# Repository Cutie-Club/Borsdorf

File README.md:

# Borsdorf
KiCad project files for the Borsdorf keyboard.

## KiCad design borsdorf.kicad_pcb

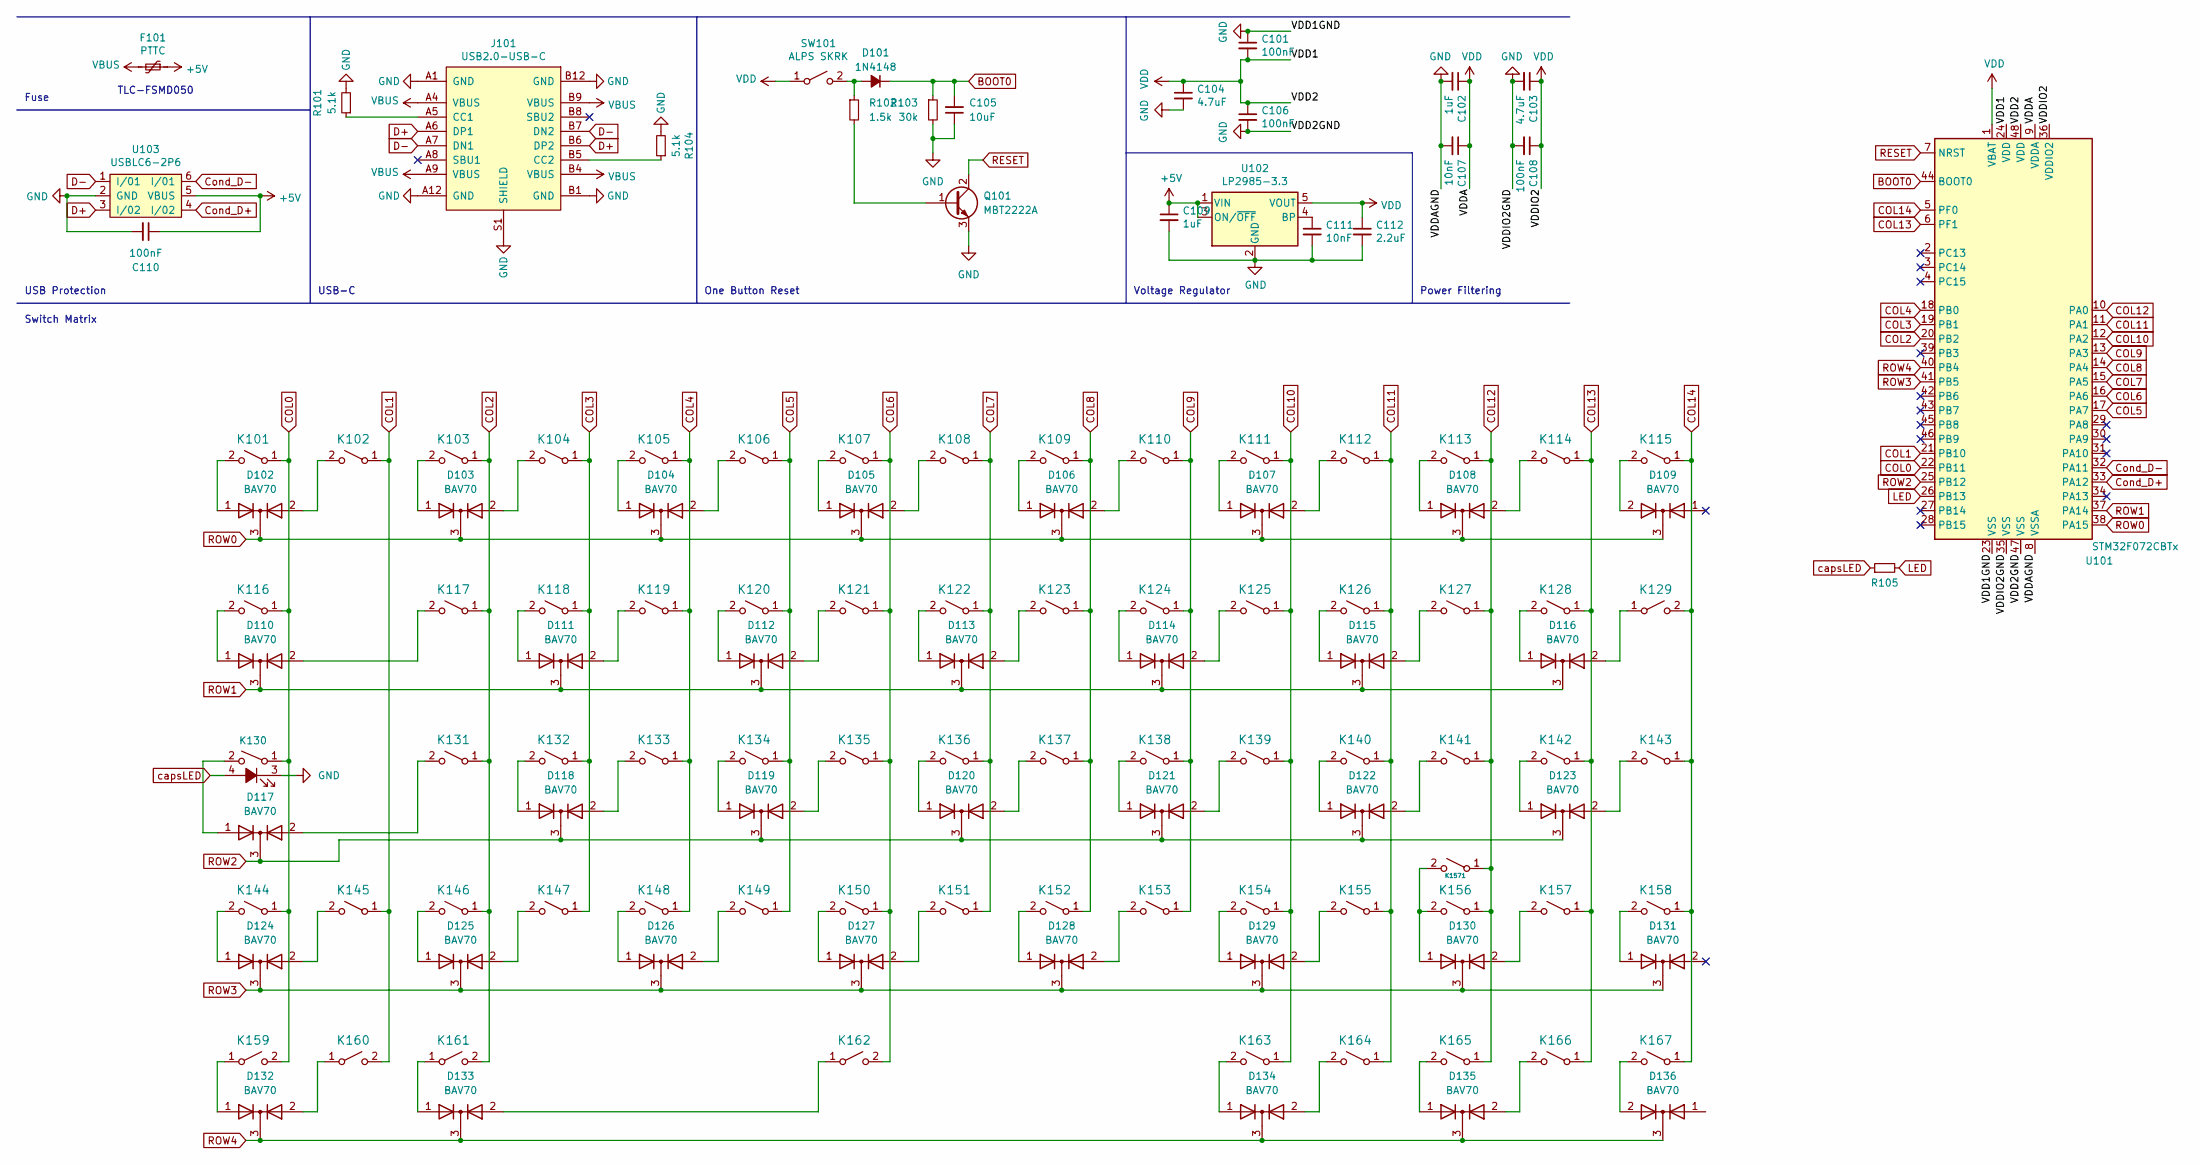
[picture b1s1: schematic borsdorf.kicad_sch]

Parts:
C101, C106, C108, C110: 100nF; C_0805_2012Metric
C102, C109: 1uF; C_0805_2012Metric
C103, C104: 4.7uF; C_0805_2012Metric
C105: 10uF; C_0805_2012Metric
C107, C111: 10nF; C_0805_2012Metric
C112: 2.2uF; C_0805_2012Metric
D101: 1N4148; D_SOD-323
D102, D103, D104, D105, D106, D107, D108, D109, D110, D111, D112, D113, D114, D115, D116, D117, D118, D119, D120, D121, D122, D123, D124, D125, D126, D127, D128, D129, D130, D131, D132, D133, D134, D135, D136: BAV70; SOT-23
F101: PTTC; Fuse_0805_2012Metric
J101: USB2.0-USB-C; USB_C_Receptacle_HRO_TYPE-C-31-M-12
K101, K102, K103, K104, K105, K106, K107, K108, K109, K110, K111, K112, K113, K114, K115, K116, K117, K118, K119, K120, K121, K122, K123, K124, K125, K126, K127, K128, K129, K131, K132, K133, K134, K135, K136, K137, K138, K139, K140, K141, K142, K143, K144, K145, K146, K147, K148, K149, K150, K151, K152, K153, K154, K155, K156, K157, K158, K159, K160, K161, K162, K163, K164, K165, K166, K167, K1571: KEYSW; Alps_SKxx_19.05mm_1.0u
K130: KEYSW; Alps_SKxx_LED_19.05mm_1.0u
Q101: MBT2222A; SOT-23-3
R101, R104: 5.1k; R_0805_2012Metric
R102: 1.5k; R_0805_2012Metric
R103: 30k; R_0805_2012Metric
R105: R_Small; R_0805_2012Metric
SW101: ALPS SKRK; ALPS_SKRK
U101: STM32F072CBTx; LQFP-48_7x7mm_P0.5mm
U102: LP2985-3.3; SOT-23-5
U103: USBLC6-2P6; SOT-23-6

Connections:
+5V: C109.1, C110.1, F101.1, U102.1 (VIN), U102.3 (ON/~OFF), U103.5 (VBUS)
BOOT0: C105.2, D101.1 (K), R103.1, U101.44 (BOOT0)
COL0: K101.1 (A), K116.1 (A), K130.1, K144.1 (A), K159.2 (B), U101.22 (PB11)
COL1: K102.1 (A), K145.1 (A), K160.2 (B), U101.21 (PB10)
COL2: K103.1 (A), K117.1 (A), K131.1 (A), K146.1 (A), K161.2 (B), U101.20 (PB2)
COL3: K104.1 (A), K118.1 (A), K132.1 (A), K147.1 (A), U101.19 (PB1)
COL4: K105.1 (A), K119.1 (A), K133.1 (A), K148.1 (A), U101.18 (PB0)
COL5: K106.1 (A), K120.1 (A), K134.1 (A), K149.1 (A), U101.17 (PA7)
COL6: K107.1 (A), K121.1 (A), K135.1 (A), K150.1 (A), K162.2 (B), U101.16 (PA6)
COL7: K108.1 (A), K122.1 (A), K136.1 (A), K151.1 (A), U101.15 (PA5)
COL8: K109.1 (A), K123.1 (A), K137.1 (A), K152.1 (A), U101.14 (PA4)
COL9: K110.1 (A), K124.1 (A), K138.1 (A), K153.1 (A), U101.13 (PA3)
COL10: K111.1 (A), K125.1 (A), K139.1 (A), K154.1 (A), K163.1 (A), U101.12 (PA2)
COL11: K112.1 (A), K126.1 (A), K140.1 (A), K155.1 (A), K164.1 (A), U101.11 (PA1)
COL12: K113.1 (A), K127.1 (A), K141.1 (A), K156.1 (A), K165.1 (A), K1571.1 (A), U101.10 (PA0)
COL13: K114.1 (A), K128.1 (A), K142.1 (A), K157.1 (A), K166.1 (A), U101.6 (PF1)
COL14: K115.1 (A), K129.2 (B), K143.1 (A), K158.1 (A), K167.1 (A), U101.5 (PF0)
Cond_D+: U101.33 (PA12), U103.4 (I/02)
Cond_D-: U101.32 (PA11), U103.6 (I/01)
D+: J101.A6 (DP1), J101.B6 (DP2), U103.3 (I/02)
D-: J101.A7 (DN1), J101.B7 (DN2), U103.1 (I/01)
GND: C101.1, C102.2, C103.2, C104.2, C105.1, C106.2, C107.2, C108.2, C109.2, C110.2, C111.2, C112.2, J101.A1 (GND), J101.A12 (GND), J101.B1 (GND), J101.B12 (GND), J101.S1 (SHIELD), K130.3 (K), Q101.3 (E), R101.2, R103.2, R104.2, U101.8 (VSSA), U101.23 (VSS), U101.35 (VSS), U101.47 (VSS), U102.2 (GND), U103.2 (GND)
LED: R105.2, U101.26 (PB13)
unnamed: C111.1, U102.4 (BP)
unnamed: D101.2 (A), R102.1, SW101.2 (B)
unnamed: D102.1 (A), K101.2 (B)
unnamed: D102.2 (A), K102.2 (B)
unnamed: D103.1 (A), K103.2 (B)
unnamed: D103.2 (A), K104.2 (B)
unnamed: D104.1 (A), K105.2 (B)
unnamed: D104.2 (A), K106.2 (B)
unnamed: D105.1 (A), K107.2 (B)
unnamed: D105.2 (A), K108.2 (B)
unnamed: D106.1 (A), K109.2 (B)
unnamed: D106.2 (A), K110.2 (B)
unnamed: D107.1 (A), K111.2 (B)
unnamed: D107.2 (A), K112.2 (B)
unnamed: D108.1 (A), K113.2 (B)
unnamed: D108.2 (A), K114.2 (B)
unnamed: D109.2 (A), K115.2 (B)
unnamed: D110.1 (A), K116.2 (B)
unnamed: D110.2 (A), K117.2 (B)
unnamed: D111.1 (A), K118.2 (B)
unnamed: D111.2 (A), K119.2 (B)
unnamed: D112.1 (A), K120.2 (B)
unnamed: D112.2 (A), K121.2 (B)
unnamed: D113.1 (A), K122.2 (B)
unnamed: D113.2 (A), K123.2 (B)
unnamed: D114.1 (A), K124.2 (B)
unnamed: D114.2 (A), K125.2 (B)
unnamed: D115.1 (A), K126.2 (B)
unnamed: D115.2 (A), K127.2 (B)
unnamed: D116.1 (A), K128.2 (B)
unnamed: D116.2 (A), K129.1 (A)
unnamed: D117.1 (A), K130.2
unnamed: D117.2 (A), K131.2 (B)
unnamed: D119.1 (A), K134.2 (B)
unnamed: D119.2 (A), K135.2 (B)
unnamed: D120.1 (A), K136.2 (B)
unnamed: D120.2 (A), K137.2 (B)
unnamed: D121.1 (A), K138.2 (B)
unnamed: D121.2 (A), K139.2 (B)
unnamed: D122.1 (A), K140.2 (B)
unnamed: D122.2 (A), K141.2 (B)
unnamed: D124.1 (A), K144.2 (B)
unnamed: D124.2 (A), K145.2 (B)
unnamed: D125.1 (A), K146.2 (B)
unnamed: D125.2 (A), K147.2 (B)
unnamed: D126.1 (A), K148.2 (B)
unnamed: D126.2 (A), K149.2 (B)
unnamed: D127.1 (A), K150.2 (B)
unnamed: D127.2 (A), K151.2 (B)
unnamed: D128.1 (A), K152.2 (B)
unnamed: D128.2 (A), K153.2 (B)
unnamed: D129.1 (A), K154.2 (B)
unnamed: D129.2 (A), K155.2 (B)
unnamed: D130.1 (A), K156.2 (B), K1571.2 (B)
unnamed: D130.2 (A), K157.2 (B)
unnamed: D131.1 (A), K158.2 (B)
unnamed: D132.1 (A), K159.1 (A)
unnamed: D132.2 (A), K160.1 (A)
unnamed: D133.1 (A), K161.1 (A)
unnamed: D133.2 (A), K162.1 (A)
unnamed: D134.1 (A), K163.2 (B)
unnamed: D134.2 (A), K164.2 (B)
unnamed: D135.1 (A), K165.2 (B)
unnamed: D135.2 (A), K166.2 (B)
unnamed: D136.2 (A), K167.2 (B)
unnamed: J101.A5 (CC1), R101.1
unnamed: J101.B5 (CC2), R104.1
unnamed: D118.1 (A), K132.2 (B)
unnamed: D118.2 (A), K133.2 (B)
unnamed: D123.1 (A), K142.2 (B)
unnamed: D123.2 (A), K143.2 (B)
unnamed: Q101.1 (B), R102.2
RESET: Q101.2 (C), U101.7 (NRST)
ROW0: D102.3 (K), D103.3 (K), D104.3 (K), D105.3 (K), D106.3 (K), D107.3 (K), D108.3 (K), D109.3 (K), U101.38 (PA15)
ROW1: D110.3 (K), D111.3 (K), D112.3 (K), D113.3 (K), D114.3 (K), D115.3 (K), D116.3 (K), U101.37 (PA14)
ROW2: D117.3 (K), D118.3 (K), D119.3 (K), D120.3 (K), D121.3 (K), D122.3 (K), D123.3 (K), U101.25 (PB12)
ROW3: D124.3 (K), D125.3 (K), D126.3 (K), D127.3 (K), D128.3 (K), D129.3 (K), D130.3 (K), D131.3 (K), U101.41 (PB5)
ROW4: D132.3 (K), D133.3 (K), D134.3 (K), D135.3 (K), D136.3 (K), U101.40 (PB4)
VBUS: F101.2, J101.A4 (VBUS), J101.A9 (VBUS), J101.B4 (VBUS), J101.B9 (VBUS)
VDD: C101.2, C102.1, C103.1, C104.1, C106.1, C107.1, C108.1, C112.1, SW101.1 (A), U101.1 (VBAT), U101.9 (VDDA), U101.24 (VDD), U101.36 (VDDIO2), U101.48 (VDD), U102.5 (VOUT)
capsLED: K130.4 (A), R105.1

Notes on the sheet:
Power Filtering
Switch Matrix
USB-C
USB Protection
TLC-FSMD050
Voltage Regulator
One Button Reset
Fuse

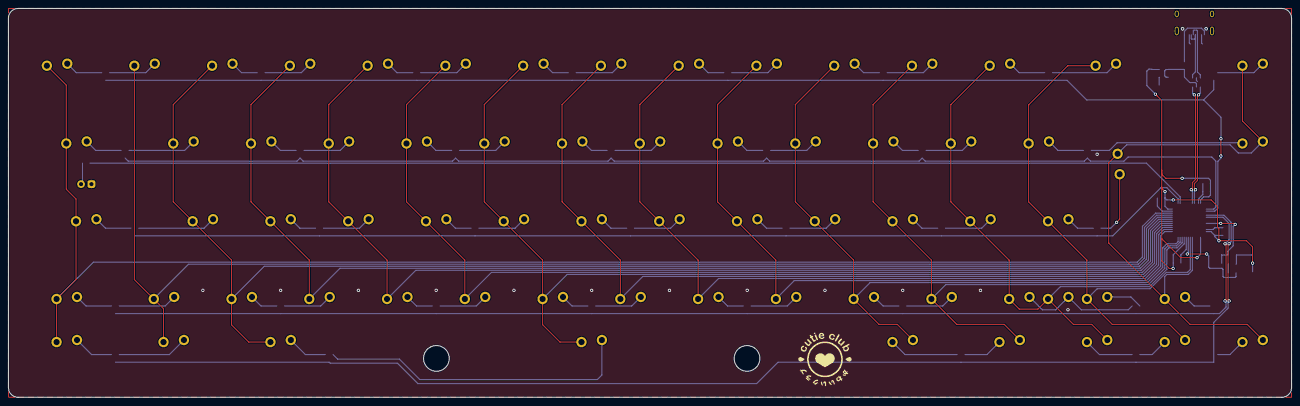
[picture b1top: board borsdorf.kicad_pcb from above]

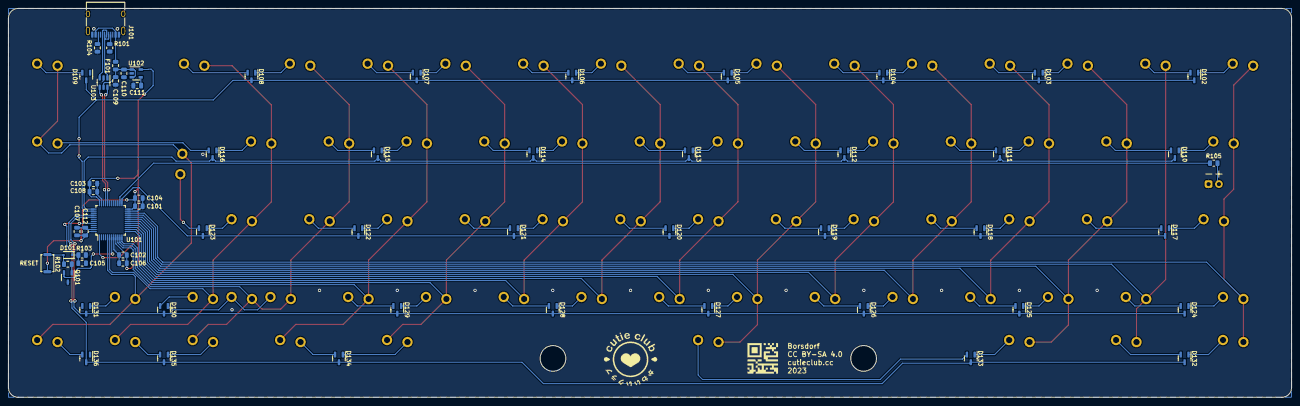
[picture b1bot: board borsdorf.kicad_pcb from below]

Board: 2 copper layers, 314.3 x 95.2 mm, 129 parts (61 on the bottom side), 104 nets.

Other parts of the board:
QR*****: 00BRDF020101

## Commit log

2019-11-01 Add licence
2019-11-01 Update gitignore
2019-11-01 Add initial project and schematic files
2020-05-02 Update to v02
2022-07-09 Update Borsdorf to production files
2023-02-22 Update files to v2/extras revision

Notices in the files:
borsdorf.kicad_pcb:
CC BY-SA 4.0
